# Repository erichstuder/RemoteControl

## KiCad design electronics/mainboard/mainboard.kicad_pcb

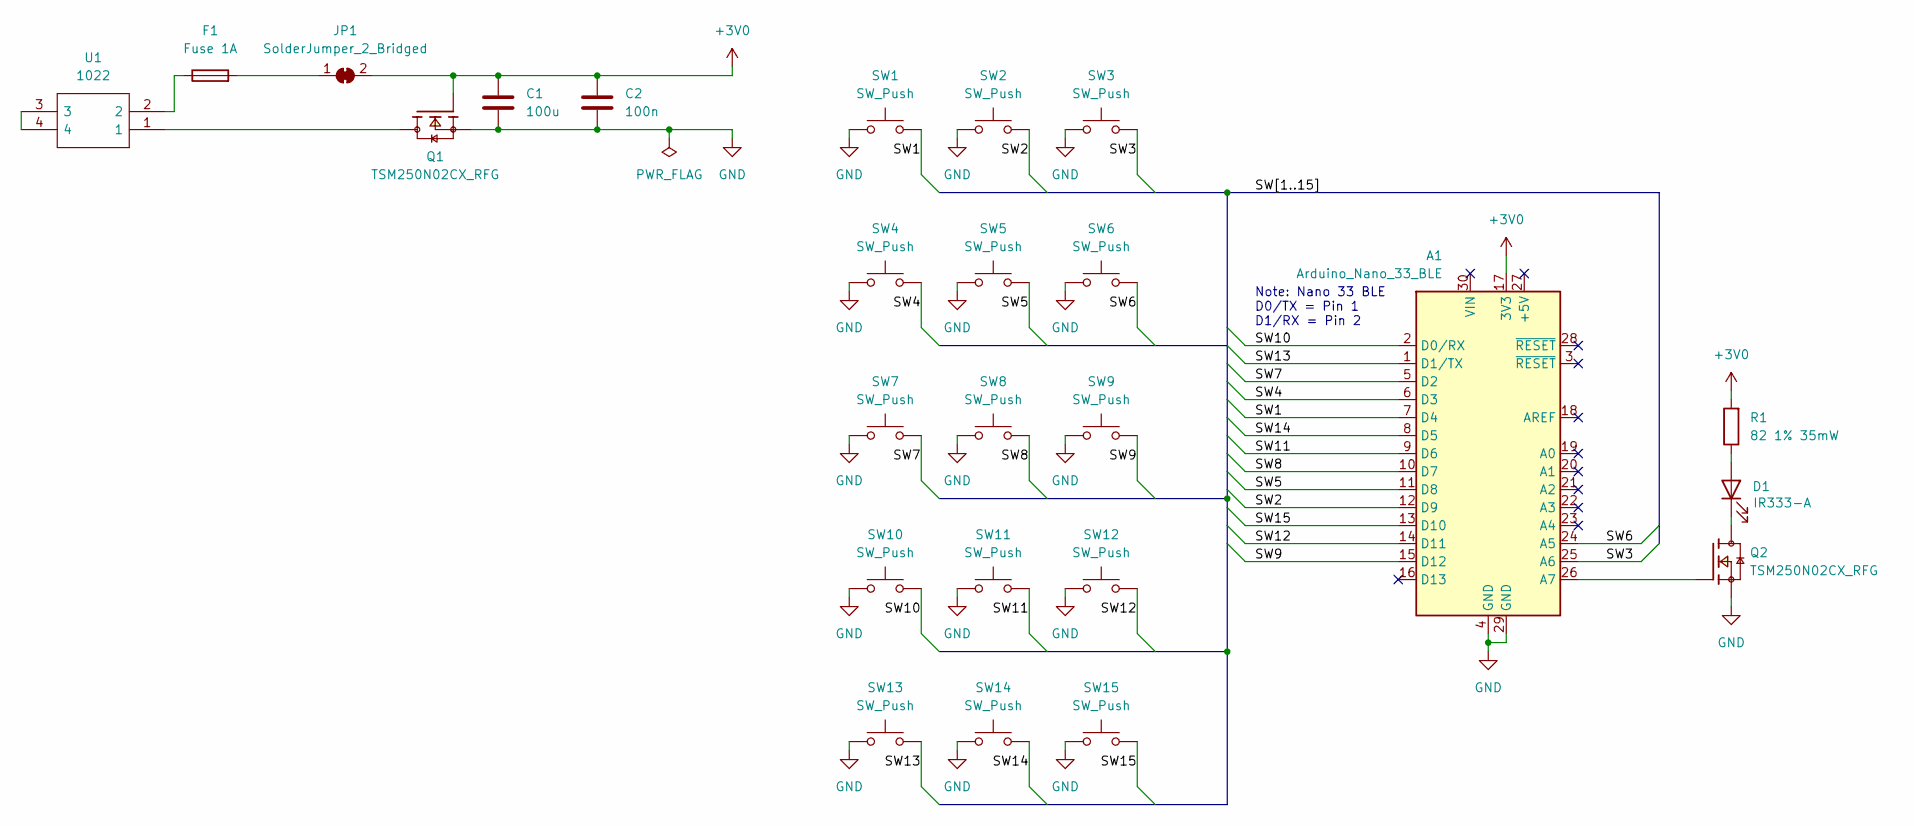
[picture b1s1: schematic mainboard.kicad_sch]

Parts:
A1: Arduino_Nano_33_BLE; Arduino_Nano_WithMountingHoles
C1: 100u; C_0805_2012Metric
C2: 100n; C_0805_2012Metric
D1: IR333-A; LED_D5.0mm_Horizontal_O1.27mm_Z3.0mm
F1: Fuse 1A; Fuse_0805_2012Metric
JP1: SolderJumper_2_Bridged; SolderJumper-2_P1.3mm_Bridged_Pad1.0x1.5mm
Q1, Q2: TSM250N02CX_RFG; TRANS_TSM250N02CX_RFG; PARTREV A2007
R1: 82 1% 35mW; R_0805_2012Metric
SW1, SW2, SW3, SW4, SW5, SW6, SW7, SW8, SW9, SW10, SW11, SW12, SW13, SW14, SW15: SW_Push; SW_PUSH_6mm
U1: 1022; Mouser Part Number 534-1022

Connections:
+3V0: A1.17 (3V3), C1.1, C2.1, JP1.2 (B), Q1.1, R1.2
/SW1: A1.7 (D4), SW1.2
/SW2: A1.12 (D9), SW2.2
/SW3: A1.25 (A6), SW3.2
/SW4: A1.6 (D3), SW4.2
/SW5: A1.11 (D8), SW5.2
/SW6: A1.24 (A5), SW6.2
/SW7: A1.5 (D2), SW7.2
/SW8: A1.10 (D7), SW8.2
/SW9: A1.15 (D12), SW9.2
/SW10: A1.2 (D0/RX), SW10.2
/SW11: A1.9 (D6), SW11.2
/SW12: A1.14 (D11), SW12.2
/SW13: A1.1 (D1/TX), SW13.2
/SW14: A1.8 (D5), SW14.2
/SW15: A1.13 (D10), SW15.2
GND: A1.4 (GND), A1.29 (GND), C1.2, C2.2, Q1.2, Q2.2, SW1.1, SW2.1, SW3.1, SW4.1, SW5.1, SW6.1, SW7.1, SW8.1, SW9.1, SW10.1, SW11.1, SW12.1, SW13.1, SW14.1, SW15.1
unnamed: A1.26 (A7), Q2.1
unnamed: D1.2 (A), R1.1
unnamed: D1.1 (K), Q2.3
unnamed: F1.1, U1.2
unnamed: F1.2, JP1.1 (A)
unnamed: Q1.3, U1.1
unnamed: U1.3, U1.4

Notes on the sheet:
Note: Nano 33 BLE D0/TX = Pin 1 D1/RX = Pin 2

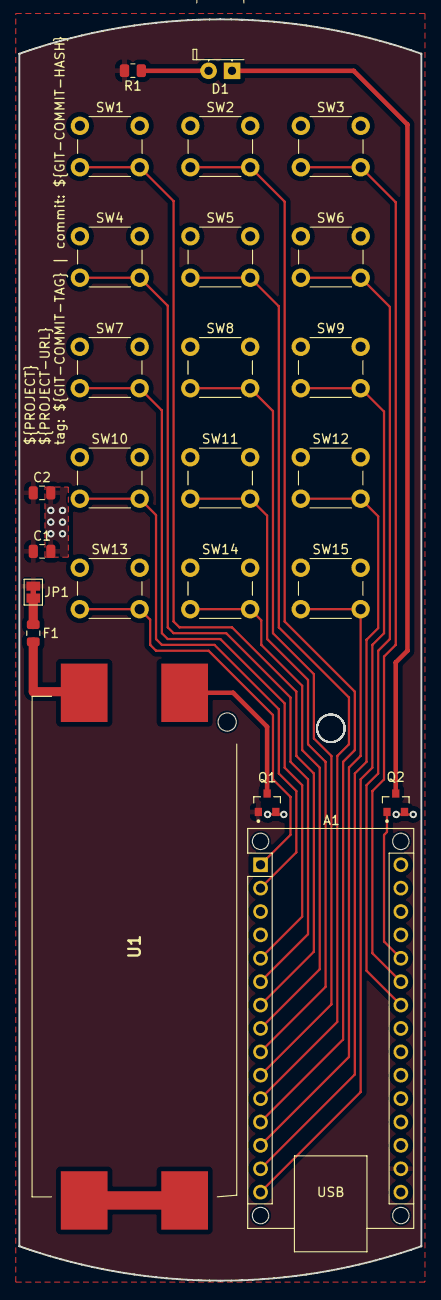
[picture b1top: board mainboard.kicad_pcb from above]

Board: 2 copper layers, 43.7 x 137.0 mm, 25 parts (0 on the bottom side), 24 nets.

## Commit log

2022-06-12 integrate workflow for automatic mainboard production data creation and releases
2022-06-12 add a fuse
2022-06-14 add 'pick and place' and bom
2022-06-14 optimize release zip file by name and by structure
2022-06-15 remove silkscreen of led that is outside the board
2022-07-05 automate firmware unit tests
2022-07-05 port firmware from breadboard to pcb
2022-07-12 integrate ble usb keyboard
2022-07-12 add init, tick and disconnect
2022-07-13 add ble remote handler
2022-07-13 add ble handler
2022-07-13 rename interface
2022-07-14 use polymorphism
2022-07-14 ble and buttons
2022-07-15 it's compiling
2022-07-15 go back to cpp for buttons
2022-07-16 bug fixes and minor improvements
2022-07-16 add note to schematic about interchanged D0 and D1
2022-08-01 integrate the keyboard - ble handling for multiple devices - improve button handling - add comment to pcb about switched D0 and D1
2022-08-01 remove unused project
2022-08-01 changed to a device
2022-08-01 bugfixing
2023-04-29 some changes
2023-04-29 use latest ubuntu
2023-04-29 use kicad v7
2023-04-29 update symbols
2023-04-29 error corrections
2023-04-29 presentation
2023-04-29 modified
2023-04-29 correct missing line
2023-04-29 minor changes
2023-04-29 make unit-test quick and dirty pass
2023-04-29 let them fail!
2023-04-29 bugfix
2023-05-10 optimize representation
2023-05-10 add more notes
2023-05-11 some modifictions
2023-05-11 correct DRC error
